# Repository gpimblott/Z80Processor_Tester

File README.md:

# Z80Processor_Tester
This is a simple tester PCB for Z80 processors.  I use it for testing processors taken from ZX81 and Spectrums that I am fixing... also to test processors that I buy online.

## Software

The software is written in MPLab X to be used on a PIC 16F690 microcontroller

## Hardware

The PCB is designed in KiCad and all the necessary files are provided to create your own version

# Versions and updates

## v01 : Hardware and Software

Initial version that cycles through the address lines by returning a NOP instructuction (all zeros) for every address.  The leds will cycle through a binary sequence until the ram refresh kicks in then it will skip about.  This is still enough to test the basic operation of the chip and has enabled me to verify several dead Z80's.

This is complete and I have had boards made at PCBWay using the .zip file in the releases tab and also included in the hardware/v01 directory.  THe PCB has a non-standard DC barrel jack footprint.  I was unable to find a component to match so I 'bodged' a normal jack.

## v02 : Hardware and Software - WIP

Do NOT use the hardware or software - this is WIP

This is an updated version that adds the following
* filters the DRAM refresh cycles
* Stop / Start buttons

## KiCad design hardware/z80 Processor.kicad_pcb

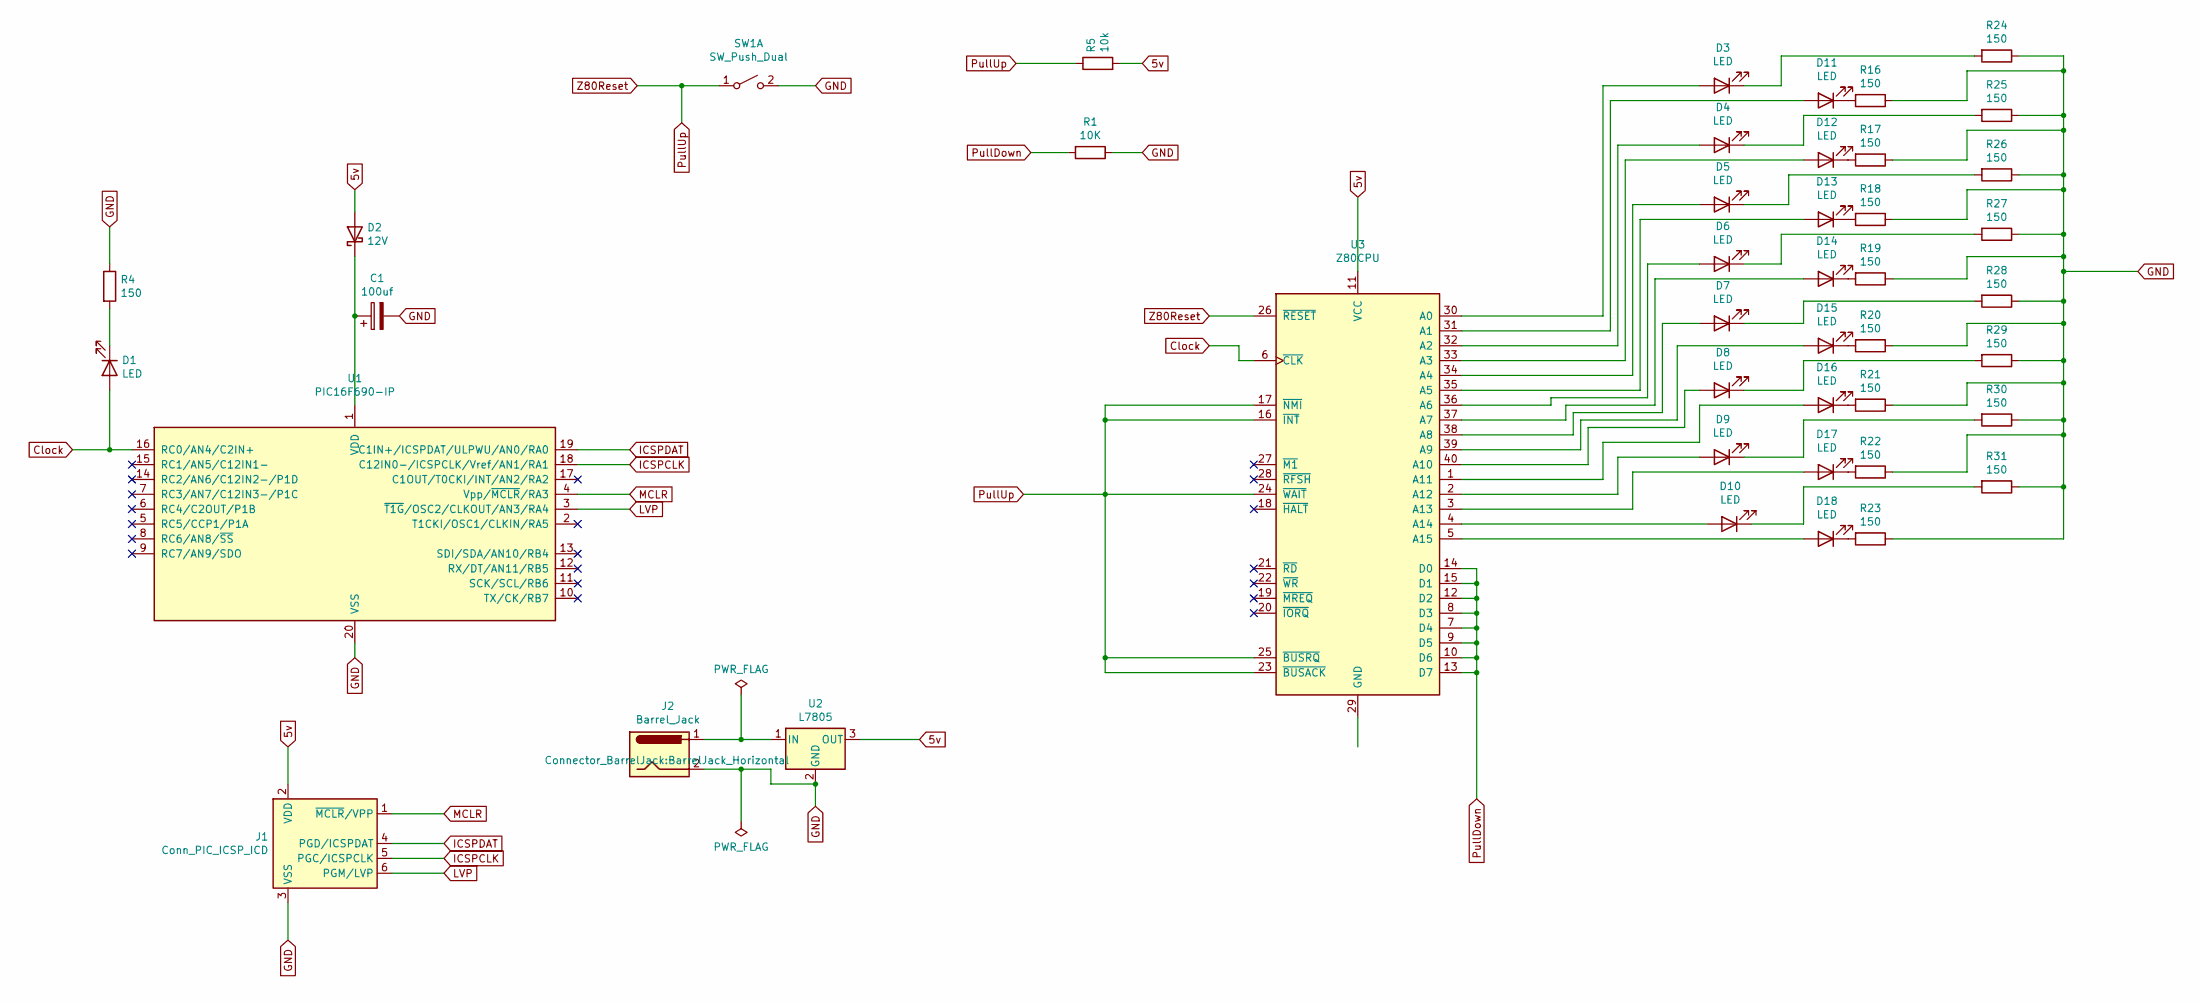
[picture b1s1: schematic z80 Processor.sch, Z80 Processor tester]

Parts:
C1: 100uf; CP_Radial_D4.0mm_P2.00mm
D1, D3, D4, D5, D6, D7, D8, D9, D10, D11, D12, D13, D14, D15, D16, D17, D18: LED; LED_D1.8mm_W3.3mm_H2.4mm
D2: 12V; D_DO-15_P10.16mm_Horizontal
J1: Conn_PIC_ICSP_ICD; PinHeader_1x06_P2.54mm_Vertical
J2: Barrel_Jack; BarrelJack_Horizontal
R1: 10K; R_Axial_DIN0204_L3.6mm_D1.6mm_P5.08mm_Horizontal
R4, R16, R17, R18, R19, R20, R21, R22, R23, R24, R25, R26, R27, R28, R29, R30, R31: 150; R_Axial_DIN0204_L3.6mm_D1.6mm_P5.08mm_Horizontal
R5: 10k; R_Axial_DIN0204_L3.6mm_D1.6mm_P5.08mm_Horizontal
SW1: SW_Push_Dual; SW_PUSH_6mm
U1: PIC16F690-IP; DIP-20_W7.62mm_Socket
U2: L7805; TO-220-3_Vertical
U3: Z80CPU; DIP_Socket-40_W11.9_W12.7_W15.24_W17.78_W18.5_3M_240-1280-0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

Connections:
5v: D2.2 (A), J1.2 (VDD), R5.2, U2.3 (OUT), U3.11 (VCC)
Clock: D1.2 (A), U1.16 (RC0/AN4/C2IN+), U3.6 (~CLK~)
GND: C1.2, J1.3 (VSS), J2.2, R1.1, R4.1, R16.1, R17.1, R18.1, R19.1, R20.1, R21.1, R22.1, R23.1, R24.1, R25.1, R26.1, R27.1, R28.1, R29.1, R30.1, R31.1, SW1.2 (B), U1.20 (VSS), U2.2 (GND)
ICSPCLK: J1.5 (PGC/ICSPCLK), U1.18 (C12IN0-/ICSPCLK/Vref/AN1/RA1)
ICSPDAT: J1.4 (PGD/ICSPDAT), U1.19 (C1IN+/ICSPDAT/ULPWU/AN0/RA0)
LVP: J1.6 (PGM/LVP), U1.3 (~T1G~/OSC2/CLKOUT/AN3/RA4)
MCLR: J1.1 (~MCLR~/VPP), U1.4 (Vpp/~MCLR~/RA3)
unnamed: C1.1, D2.1 (K), U1.1 (VDD)
unnamed: D1.1 (K), R4.2
unnamed: D3.1 (K), R24.2
unnamed: D3.2 (A), U3.30 (A0)
unnamed: D4.1 (K), R25.2
unnamed: D4.2 (A), U3.32 (A2)
unnamed: D5.1 (K), R26.2
unnamed: D5.2 (A), U3.34 (A4)
unnamed: D6.1 (K), R27.2
unnamed: D6.2 (A), U3.36 (A6)
unnamed: D7.1 (K), R28.2
unnamed: D7.2 (A), U3.38 (A8)
unnamed: D8.1 (K), R29.2
unnamed: D8.2 (A), U3.40 (A10)
unnamed: D9.1 (K), R30.2
unnamed: D9.2 (A), U3.2 (A12)
unnamed: D10.1 (K), R31.2
unnamed: D10.2 (A), U3.4 (A14)
unnamed: D11.1 (K), R16.2
unnamed: D11.2 (A), U3.31 (A1)
unnamed: D12.1 (K), R17.2
unnamed: D12.2 (A), U3.33 (A3)
unnamed: D13.1 (K), R18.2
unnamed: D13.2 (A), U3.35 (A5)
unnamed: D14.1 (K), R19.2
unnamed: D14.2 (A), U3.37 (A7)
unnamed: D15.1 (K), R20.2
unnamed: D15.2 (A), U3.39 (A9)
unnamed: D16.1 (K), R21.2
unnamed: D16.2 (A), U3.1 (A11)
unnamed: D17.1 (K), R22.2
unnamed: D17.2 (A), U3.3 (A13)
unnamed: D18.1 (K), R23.2
unnamed: D18.2 (A), U3.5 (A15)
unnamed: J2.1, U2.1 (IN)
PullDown: R1.2, U3.7 (D4), U3.8 (D3), U3.9 (D5), U3.10 (D6), U3.12 (D2), U3.13 (D7), U3.14 (D0), U3.15 (D1)
PullUp: R5.1, SW1.1 (A), U3.16 (~INT~), U3.17 (~NMI~), U3.23 (~BUSACK~), U3.24 (~WAIT~), U3.25 (~BUSRQ~), U3.26 (~RESET~)

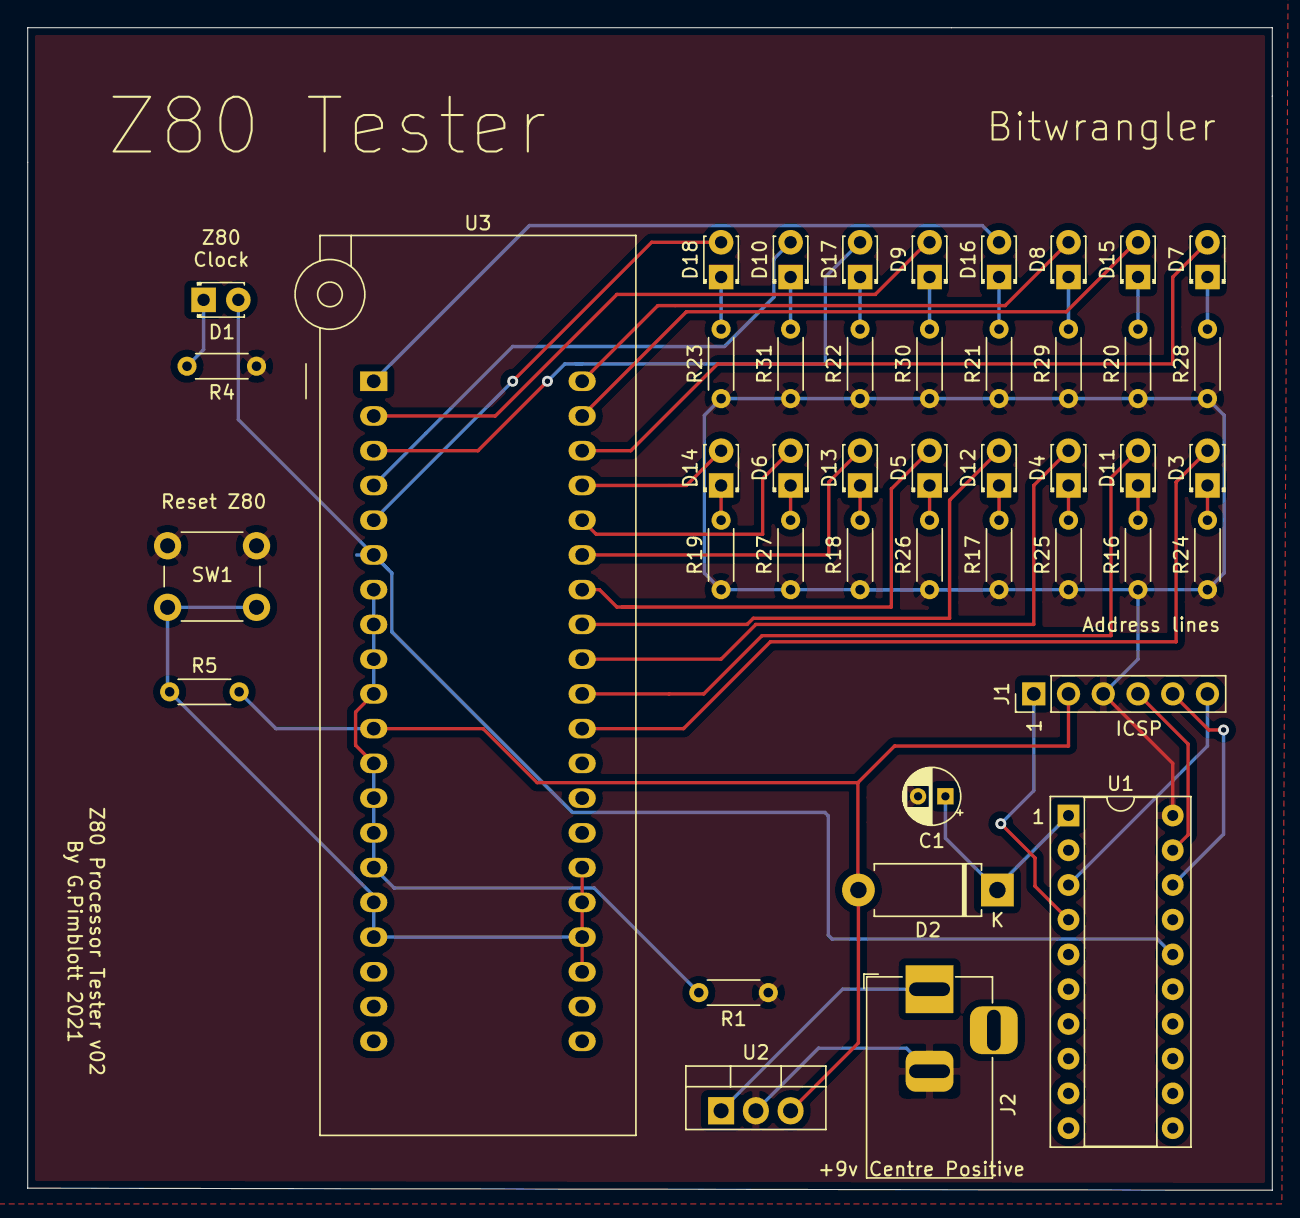
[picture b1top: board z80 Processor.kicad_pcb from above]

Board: 2 copper layers, 91.0 x 85.0 mm, 44 parts (0 on the bottom side), 44 nets.

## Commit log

2021-07-04 Initial push og v1 schematics
2021-07-04 Added V1 Software
2021-07-04 Standards hardware and software directory structure
2021-07-04 Added V02 software to project and updated ignore file
2021-07-04 Added images of v01 board
2021-07-04 rename images
2021-08-05 Update README.md
    Warning about the barrel jack
2021-09-04 Update speed to run 10 times faster
2021-09-04 Update to speed of test

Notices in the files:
hardware/z80 Processor.kicad_pcb:
License:
